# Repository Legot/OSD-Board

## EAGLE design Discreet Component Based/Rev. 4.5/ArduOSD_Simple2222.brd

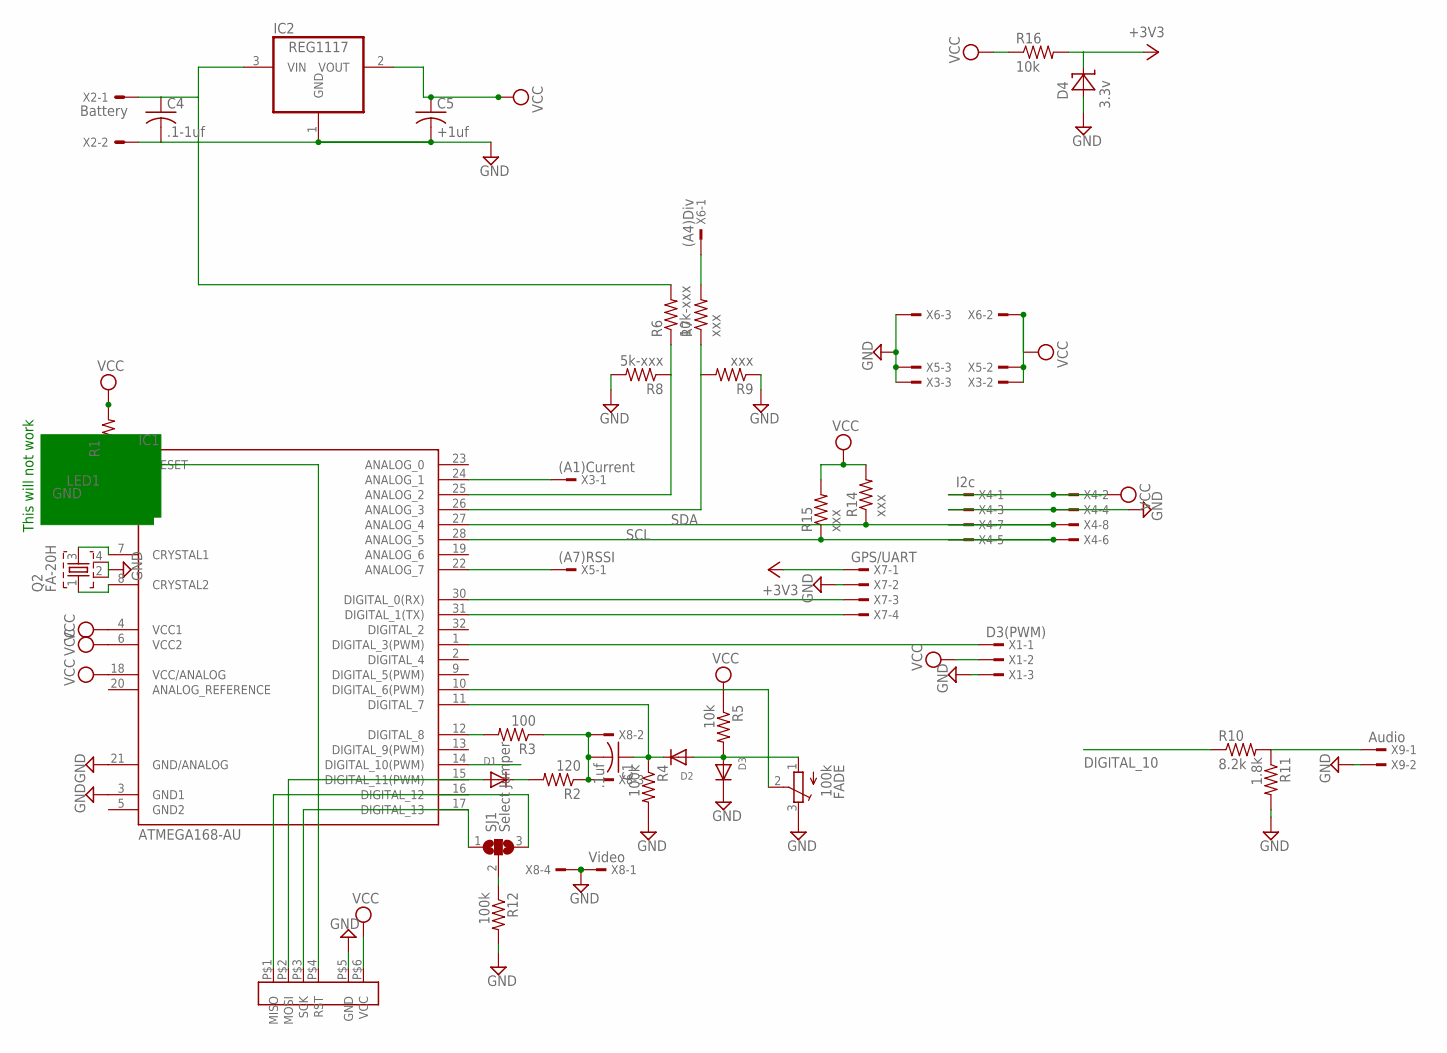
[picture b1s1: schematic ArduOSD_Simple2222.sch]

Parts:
C1: .1uf; C0805K
C4: .1-1uf; C0805K
C5: +1uf; C0805K
D1, D2, D3: DIODESOT23_WAVE; SOT23-W
D4: 3.3v; SOD-123
FADE: 100k; TC33X
IC1: ATMEGA168-AU; TQFP32-08
IC2: REG1117; SOT223
LED1: LEDCHIP-LED0805; CHIP-LED0805
Q2: FA-20H
R1: R-US_R0805; R0805
R2: 120; R0805
R3: 100; R0805
R4, R12: 100k; R0805
R5, R16: 10k; R0805
R6: 10k-xxx; R0805
R7, R9, R14, R15: xxx; R0805
R8: 5k-xxx; R0805
R10: 8.2k; R0805
R11: 1.8k; R0805
SJ1: Select Jumper; SJ_2
U$1: LIN_ISP; LINEAR_ISP
X1: D3(PWM); TSW-103-02-S-S
X2: Battery; 22-23-2021
X3: (A1)Current; TSW-103-02-S-S
X4: I2c; TSW-104-02-S-D-RA
X5: (A7)RSSI; TSW-103-02-S-S
X6: (A4)Div; TSW-103-02-S-S
X7: GPS/UART; TSW-104-02-S-S-RA
X8: Video; TSW-104-02-S-S-RA
X9: Audio; TSW-102-02-S-S-RA

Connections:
+3V3: D4.1 (C), R16.2, X7.1
AAAAAAAAAAAAHHHHHHHHHHHHH: R10.2, R11.1, X9.1
BATT_FPV: C4.1, IC2.3 (VIN), R6.2, X2.1
DIGITAL_10: IC1.14 (DIGITAL_10(PWM)), R10.1
GND: C4.2, C5.2, D3.3 (C), D4.2 (A), FADE.3 (E), IC1.3 (GND1), IC1.21 (GND/ANALOG), IC2.1 (GND), LED1.C, Q2.2, Q2.4, R4.2, R8.2, R9.1, R11.2, R12.2, U$1.P$5 (GND), X1.3, X2.2, X3.3, X4.3, X4.4, X5.3, X6.3, X7.2, X8.1, X8.4, X9.2
GND2: IC1.5 (GND2)
unnamed: IC1.29 (RESET), LED1.A, R1.1, U$1.P$4 (RST)
unnamed: D1.1 (A), IC1.15 (DIGITAL_11(PWM)), U$1.P$2 (MOSI)
unnamed: D1.3 (C), R2.2
unnamed: IC1.12 (DIGITAL_8), R3.2
unnamed: C1.2, R2.1, R3.1, X8.2, X8.3
unnamed: C1.1, D2.3 (C), IC1.11 (DIGITAL_7), R4.1
unnamed: D2.1 (A), D3.1 (A), FADE.1 (A), R5.2
unnamed: FADE.2 (S), IC1.10 (DIGITAL_6(PWM))
unnamed: IC1.26 (ANALOG_3), R7.1, R9.2
unnamed: IC1.7 (CRYSTAL1), Q2.3
unnamed: R12.1, SJ1.2
unnamed: R7.2, X6.1
unnamed: IC1.22 (ANALOG_7), X5.1
unnamed: IC1.16 (DIGITAL_12), SJ1.3, U$1.P$1 (MISO)
unnamed: IC1.17 (DIGITAL_13), SJ1.1, U$1.P$3 (SCK)
unnamed: IC1.24 (ANALOG_1), X3.1
unnamed: IC1.1 (DIGITAL_3(PWM)), X1.1
unnamed: IC1.25 (ANALOG_2), R6.1, R8.1
unnamed: IC1.8 (CRYSTAL2), Q2.1
RX: IC1.30 (DIGITAL_0(RX)), X7.3
SCL: IC1.28 (ANALOG_5), R15.1, X4.5, X4.6
SDA: IC1.27 (ANALOG_4), R14.1, X4.7, X4.8
TX: IC1.31 (DIGITAL_1(TX)), X7.4
VCC: C5.1, IC1.4 (VCC1), IC1.6 (VCC2), IC1.18 (VCC/ANALOG), IC2.2 (VOUT), R1.2, R5.1, R14.2, R15.2, R16.1, U$1.P$6 (VCC), X1.2, X3.2, X4.1, X4.2, X5.2, X6.2

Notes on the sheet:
This will not work

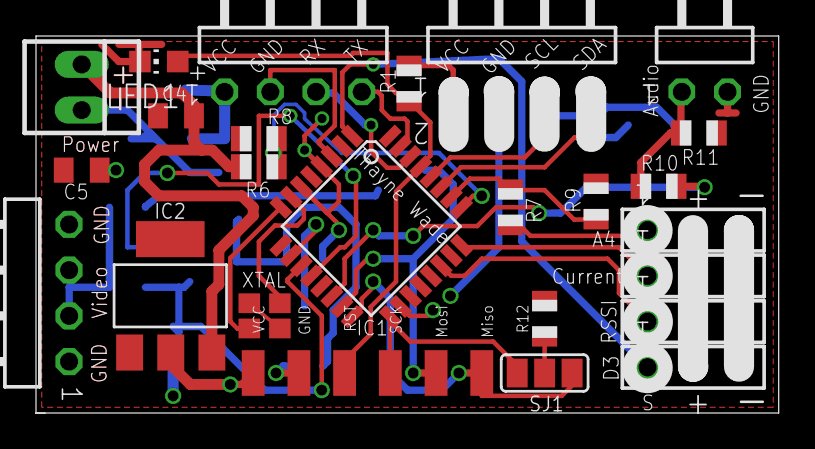
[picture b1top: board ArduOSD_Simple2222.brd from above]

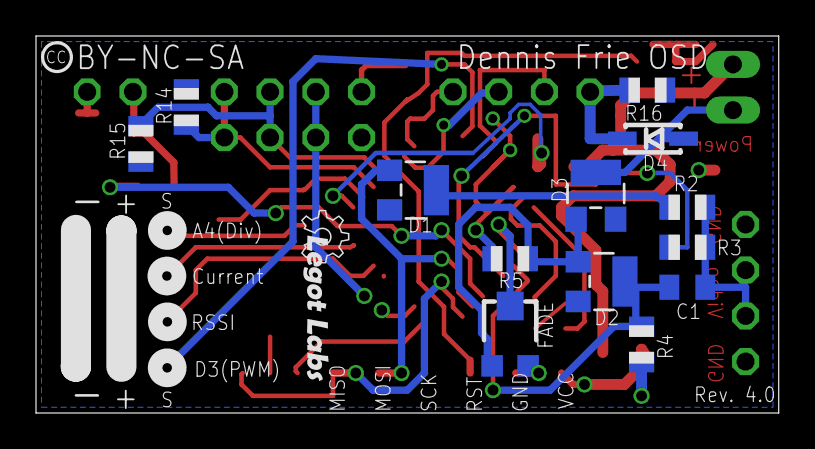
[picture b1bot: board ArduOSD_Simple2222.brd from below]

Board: 2 copper layers, 41.3 x 20.9 mm, 38 parts (13 on the bottom side), 29 nets.

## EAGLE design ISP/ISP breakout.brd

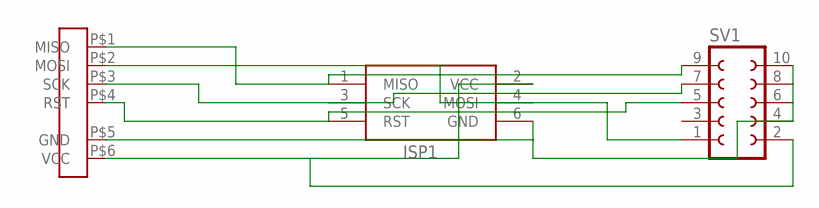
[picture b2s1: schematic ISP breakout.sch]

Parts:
ISP1: AVRISP-6; AVRISP
SV1: FE05-2
U$1: LIN_ISP; LINEAR_ISP

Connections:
unnamed: ISP1.2 (VCC), SV1.2, U$1.P$6 (VCC)
unnamed: ISP1.4 (MOSI), SV1.1, U$1.P$2 (MOSI)
unnamed: ISP1.1 (MISO), SV1.9, U$1.P$1 (MISO)
unnamed: ISP1.3 (SCK), SV1.7, U$1.P$3 (SCK)
unnamed: ISP1.5 (RST), SV1.5, U$1.P$4 (RST)
unnamed: ISP1.6 (GND), SV1.4, SV1.6, SV1.8, SV1.10, U$1.P$5 (GND)

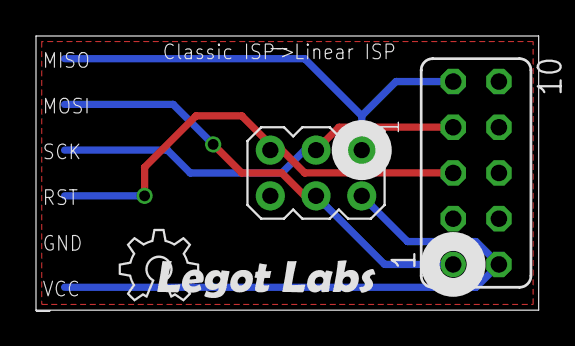
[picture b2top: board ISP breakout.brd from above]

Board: 2 copper layers, 27.9 x 15.2 mm, 3 parts (1 on the bottom side), 6 nets.

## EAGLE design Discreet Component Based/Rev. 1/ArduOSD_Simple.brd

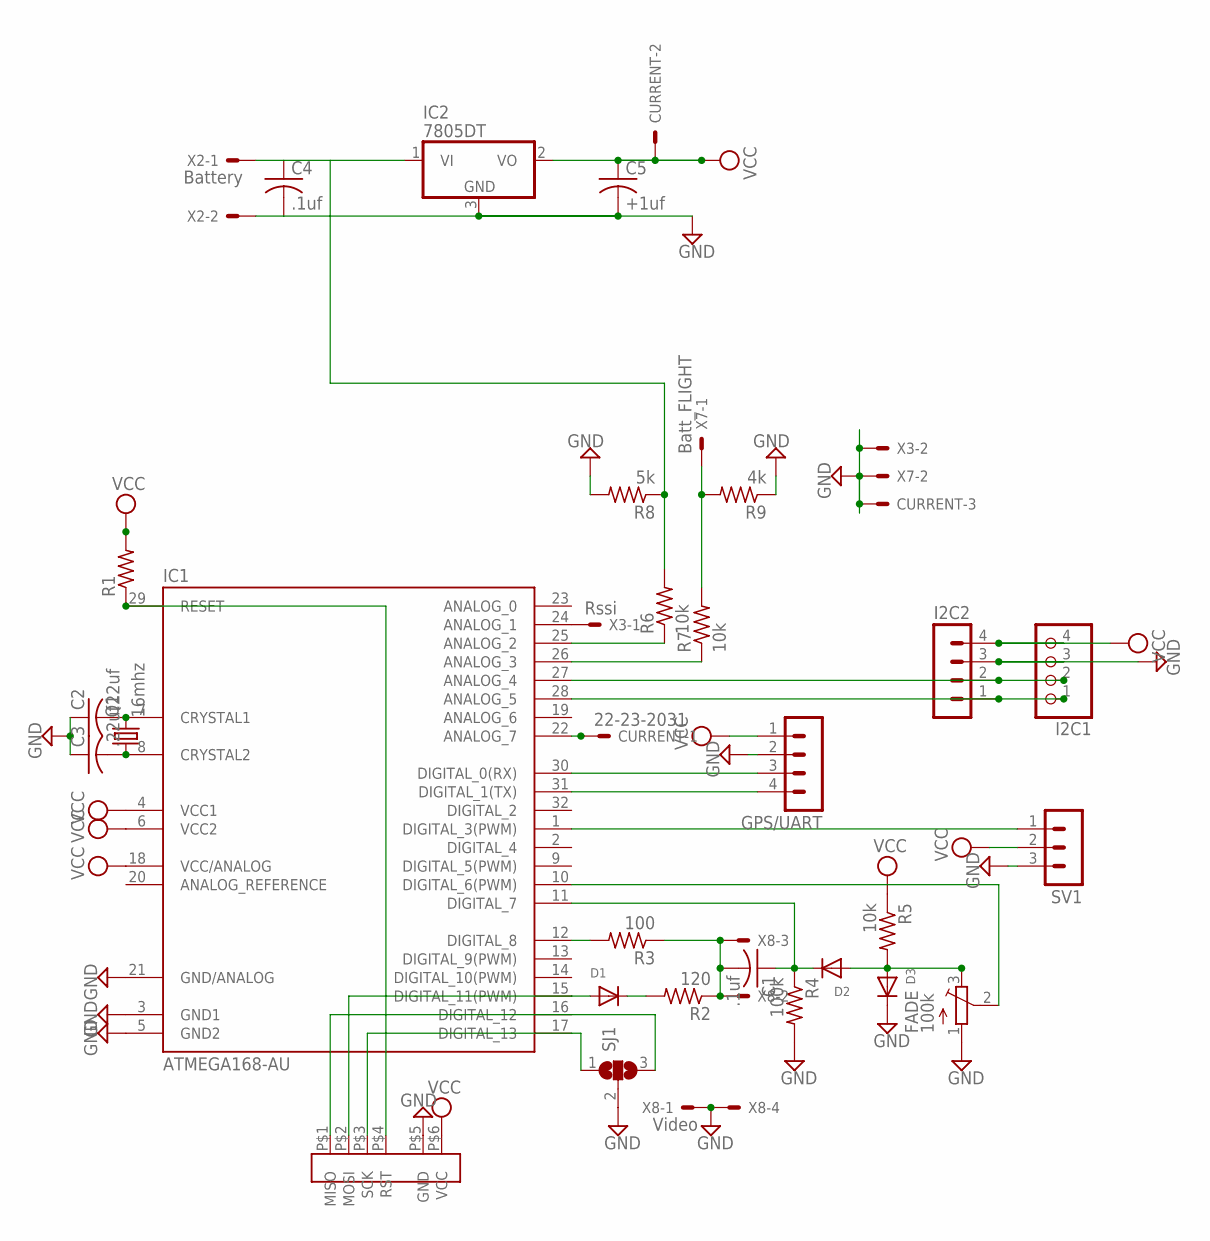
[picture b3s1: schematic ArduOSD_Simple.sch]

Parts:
C1, C4: .1uf; C0805K
C2, C3: .22uf; C0805K
C5: +1uf; C0805K
CURRENT: 22-23-2031
D1, D2, D3: DIODESOT23_WAVE; SOT23-W
FADE: 100k; TC33X
GPS/UART: MA04-1
I2C1: PINHD-1X4; 1X04
I2C2: MA04-1
IC1: ATMEGA168-AU; TQFP32-08
IC2: 7805DT; TO252
Q1: 16mhz; CSM-7X-DU
R1: R-US_R0805; R0805
R2: 120; R0805
R3: 100; R0805
R4: 100k; R0805
R5, R6, R7: 10k; R0805
R8: 5k; R0805
R9: 4k; R0805
SJ1: SJ2W; SJ_2
SV1: MA03-1
U$1: LIN_ISP; LINEAR_ISP
X2: Battery; 22-23-2021
X3: Rssi; 22-23-2021
X7: Batt_FLIGHT; 22-23-2021
X8: Video; 22-23-2041

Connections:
BATT_FPV: C4.1, IC2.1 (VI), R6.2, R8.1, X2.1
GND: C2.1, C3.1, C4.2, C5.2, CURRENT.3, D3.3 (C), FADE.1 (A), GPS/UART.2, I2C1.3, I2C2.3, IC1.3 (GND1), IC1.5 (GND2), IC1.21 (GND/ANALOG), IC2.3 (GND), R4.2, R8.2, R9.1, SJ1.2, SV1.3, U$1.P$5 (GND), X2.2, X3.2, X7.2, X8.1, X8.4
GPS_DAT: GPS/UART.3, IC1.30 (DIGITAL_0(RX))
unnamed: IC1.29 (RESET), R1.1, U$1.P$4 (RST)
unnamed: D1.1 (A), IC1.15 (DIGITAL_11(PWM)), U$1.P$2 (MOSI)
unnamed: D1.3 (C), R2.2
unnamed: IC1.12 (DIGITAL_8), R3.2
unnamed: C1.2, R2.1, R3.1, X8.2, X8.3
unnamed: C1.1, D2.3 (C), IC1.11 (DIGITAL_7), R4.1
unnamed: D2.1 (A), D3.1 (A), FADE.3 (E), R5.2
unnamed: FADE.2 (S), IC1.10 (DIGITAL_6(PWM))
unnamed: GPS/UART.4, IC1.31 (DIGITAL_1(TX))
unnamed: IC1.26 (ANALOG_3), R7.1
unnamed: C2.2, IC1.7 (CRYSTAL1), Q1.2
unnamed: C3.2, IC1.8 (CRYSTAL2), Q1.1
unnamed: IC1.25 (ANALOG_2), R6.1
unnamed: IC1.24 (ANALOG_1), X3.1
unnamed: IC1.16 (DIGITAL_12), SJ1.3, U$1.P$1 (MISO)
unnamed: IC1.17 (DIGITAL_13), SJ1.1, U$1.P$3 (SCK)
unnamed: CURRENT.1, IC1.22 (ANALOG_7)
unnamed: IC1.1 (DIGITAL_3(PWM)), SV1.1
unnamed: R7.2, R9.2, X7.1
SCL: I2C1.1, I2C2.1, IC1.28 (ANALOG_5)
SDA: I2C1.2, I2C2.2, IC1.27 (ANALOG_4)
VCC: C5.1, CURRENT.2, GPS/UART.1, I2C1.4, I2C2.4, IC1.4 (VCC1), IC1.6 (VCC2), IC1.18 (VCC/ANALOG), IC2.2 (VO), R1.2, R5.1, SV1.2, U$1.P$6 (VCC)

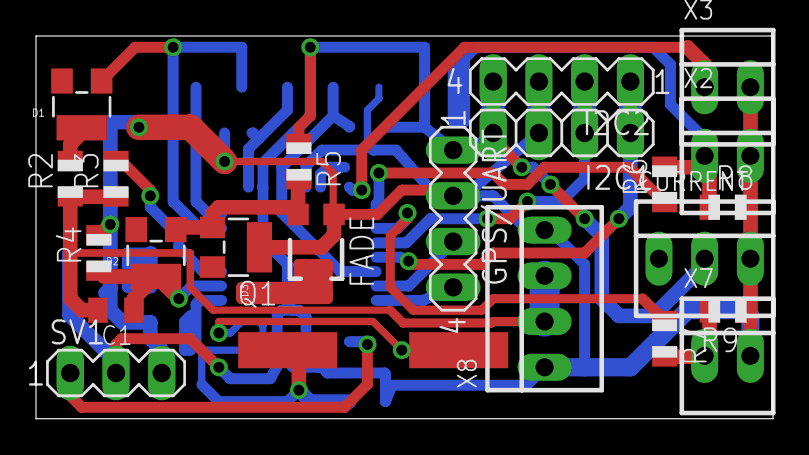
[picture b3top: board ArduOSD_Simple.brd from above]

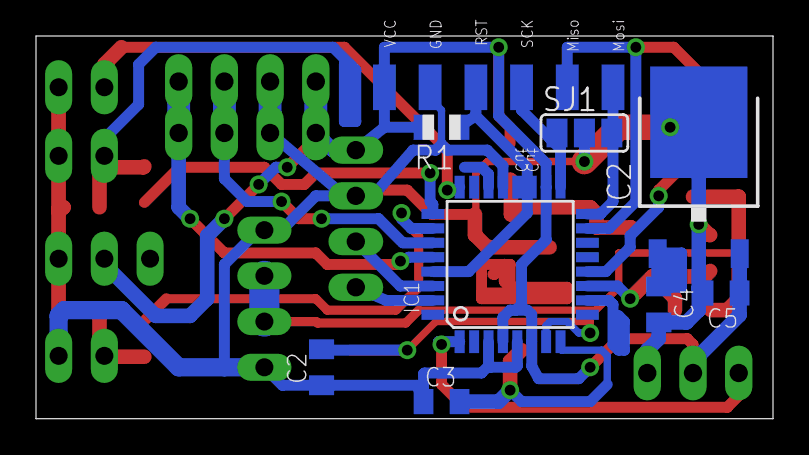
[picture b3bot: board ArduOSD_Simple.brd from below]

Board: 2 copper layers, 40.9 x 21.3 mm, 32 parts (9 on the bottom side), 25 nets.

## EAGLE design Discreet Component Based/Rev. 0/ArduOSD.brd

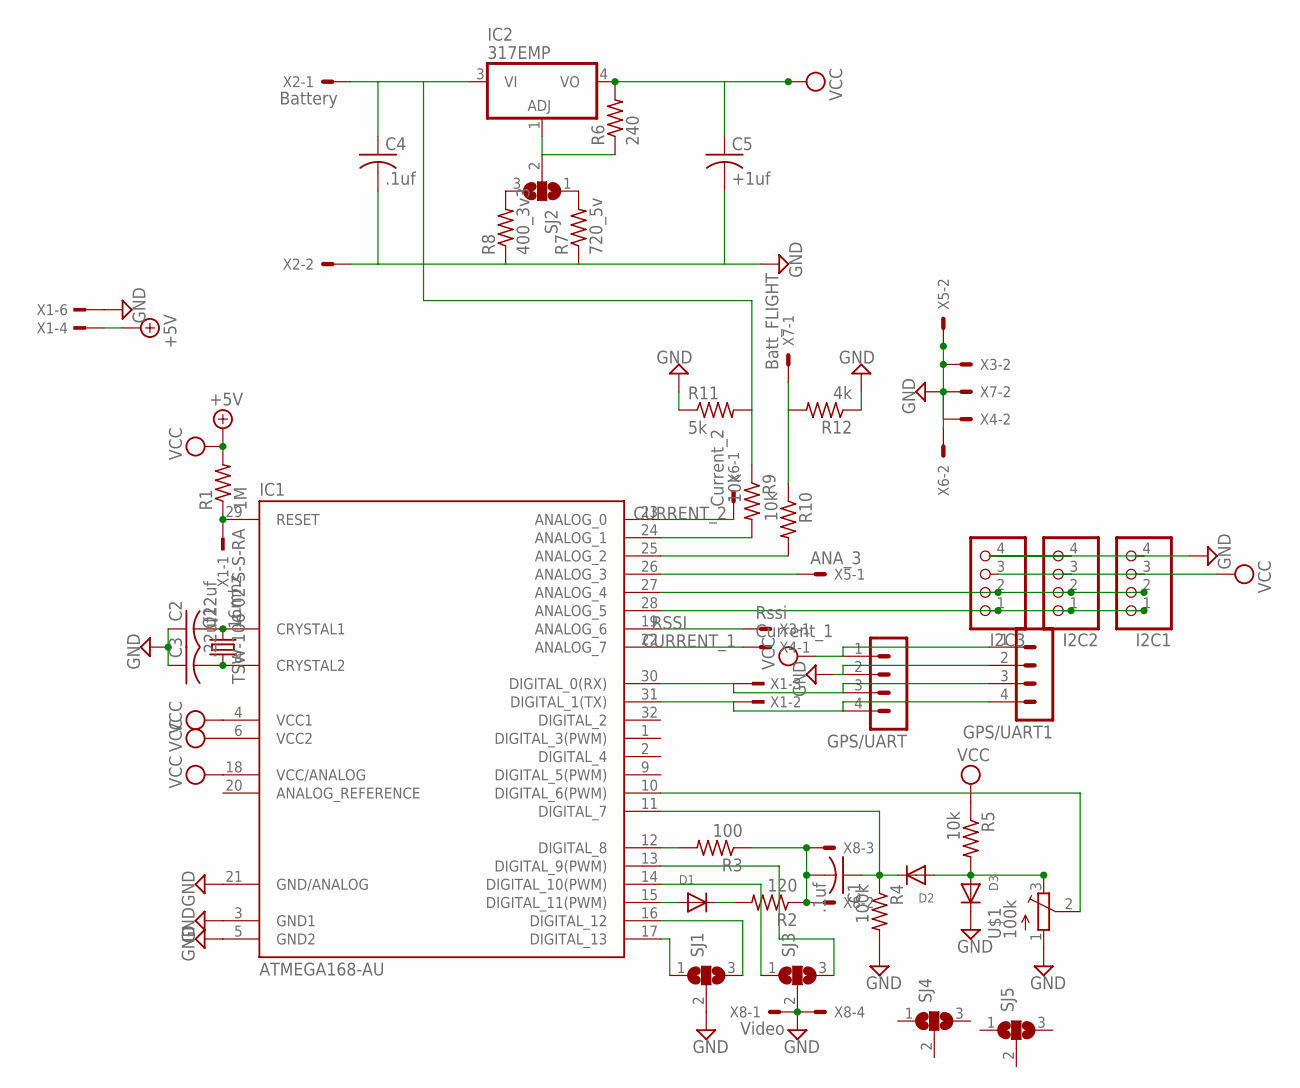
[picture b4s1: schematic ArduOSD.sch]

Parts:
C1, C4: .1uf; C0805K
C2, C3: .22uf; C0805K
C5: +1uf; C025-060X050
D1, D2, D3: DIODESOT23_WAVE; SOT23-W
GPS/UART, GPS/UART1: MA04-1
I2C1, I2C2, I2C3: PINHD-1X4; 1X04
IC1: ATMEGA168-AU; TQFP32-08
IC2: 317EMP; SOT223
Q1: 16mhz; CSM-7X-DU
R1: 1M; M0805
R2: 120; M0805
R3: 100; M0805
R4: 100k; M0805
R5, R9, R10: 10k; M0805
R6: 240; R0805
R7: 720_5v; R0805
R8: 400_3v3; R0805
R11: 5k; M0805
R12: 4k; M0805
SJ1, SJ2, SJ3, SJ4, SJ5: SJ2W; SJ_2
U$1: 100k; TC33X
X1: TSW-106-02-S-S-RA
X2: Battery; 22-23-2021
X3: Rssi; 22-23-2021
X4: Current_1; 22-23-2021
X5: ANA_3; 22-23-2021
X6: Current_2; 22-23-2021
X7: Batt_FLIGHT; 22-23-2021
X8: Video; 22-23-2041

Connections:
+5V: X1.4
ANA_3: IC1.26 (ANALOG_3), X5.1
BATT_FPV: C4.1, IC2.3 (VI), R9.1, R11.2, X2.1
CURRENT_1: IC1.22 (ANALOG_7), X4.1
CURRENT_2: IC1.23 (ANALOG_0), X6.1
GND: C2.1, C3.1, C4.2, C5.2, D3.3 (C), GPS/UART.2, GPS/UART1.2, I2C1.4, I2C2.4, I2C3.4, IC1.3 (GND1), IC1.5 (GND2), IC1.21 (GND/ANALOG), R4.2, R7.1, R8.1, R11.1, R12.1, SJ1.2, SJ3.2, U$1.1 (A), X1.6, X2.2, X3.2, X4.2, X5.2, X6.2, X7.2, X8.1, X8.4
GPS_DAT: GPS/UART.3, GPS/UART1.3, IC1.30 (DIGITAL_0(RX)), X1.3
unnamed: IC1.29 (RESET), R1.1, X1.1
unnamed: D1.1 (A), IC1.15 (DIGITAL_11(PWM))
unnamed: D1.3 (C), R2.2
unnamed: IC1.12 (DIGITAL_8), R3.2
unnamed: C1.2, R2.1, R3.1, X8.2, X8.3
unnamed: C1.1, D2.3 (C), IC1.11 (DIGITAL_7), R4.1
unnamed: D2.1 (A), D3.1 (A), R5.2, U$1.3 (E)
unnamed: IC1.10 (DIGITAL_6(PWM)), U$1.2 (S)
unnamed: GPS/UART.4, GPS/UART1.4, IC1.31 (DIGITAL_1(TX)), X1.2
unnamed: C2.2, IC1.7 (CRYSTAL1), Q1.2
unnamed: C3.2, IC1.8 (CRYSTAL2), Q1.1
unnamed: IC1.25 (ANALOG_2), R10.2
unnamed: IC1.24 (ANALOG_1), R9.2
unnamed: IC1.16 (DIGITAL_12), SJ1.3
unnamed: IC1.17 (DIGITAL_13), SJ1.1
unnamed: IC2.1 (ADJ), R6.1, SJ2.2
unnamed: R7.2, SJ2.1
unnamed: R10.1, R12.2, X7.1
unnamed: R8.2, SJ2.3
unnamed: IC1.14 (DIGITAL_10(PWM)), SJ3.1
unnamed: IC1.13 (DIGITAL_9(PWM)), SJ3.3
RSSI: IC1.19 (ANALOG_6), X3.1
SCL: I2C1.1, I2C2.1, I2C3.1, IC1.28 (ANALOG_5)
SDA: I2C1.2, I2C2.2, I2C3.2, IC1.27 (ANALOG_4)
VCC: C5.1, GPS/UART.1, GPS/UART1.1, I2C1.3, I2C2.3, I2C3.3, IC1.4 (VCC1), IC1.6 (VCC2), IC1.18 (VCC/ANALOG), IC2.4 (VO), R1.2, R5.1, R6.2

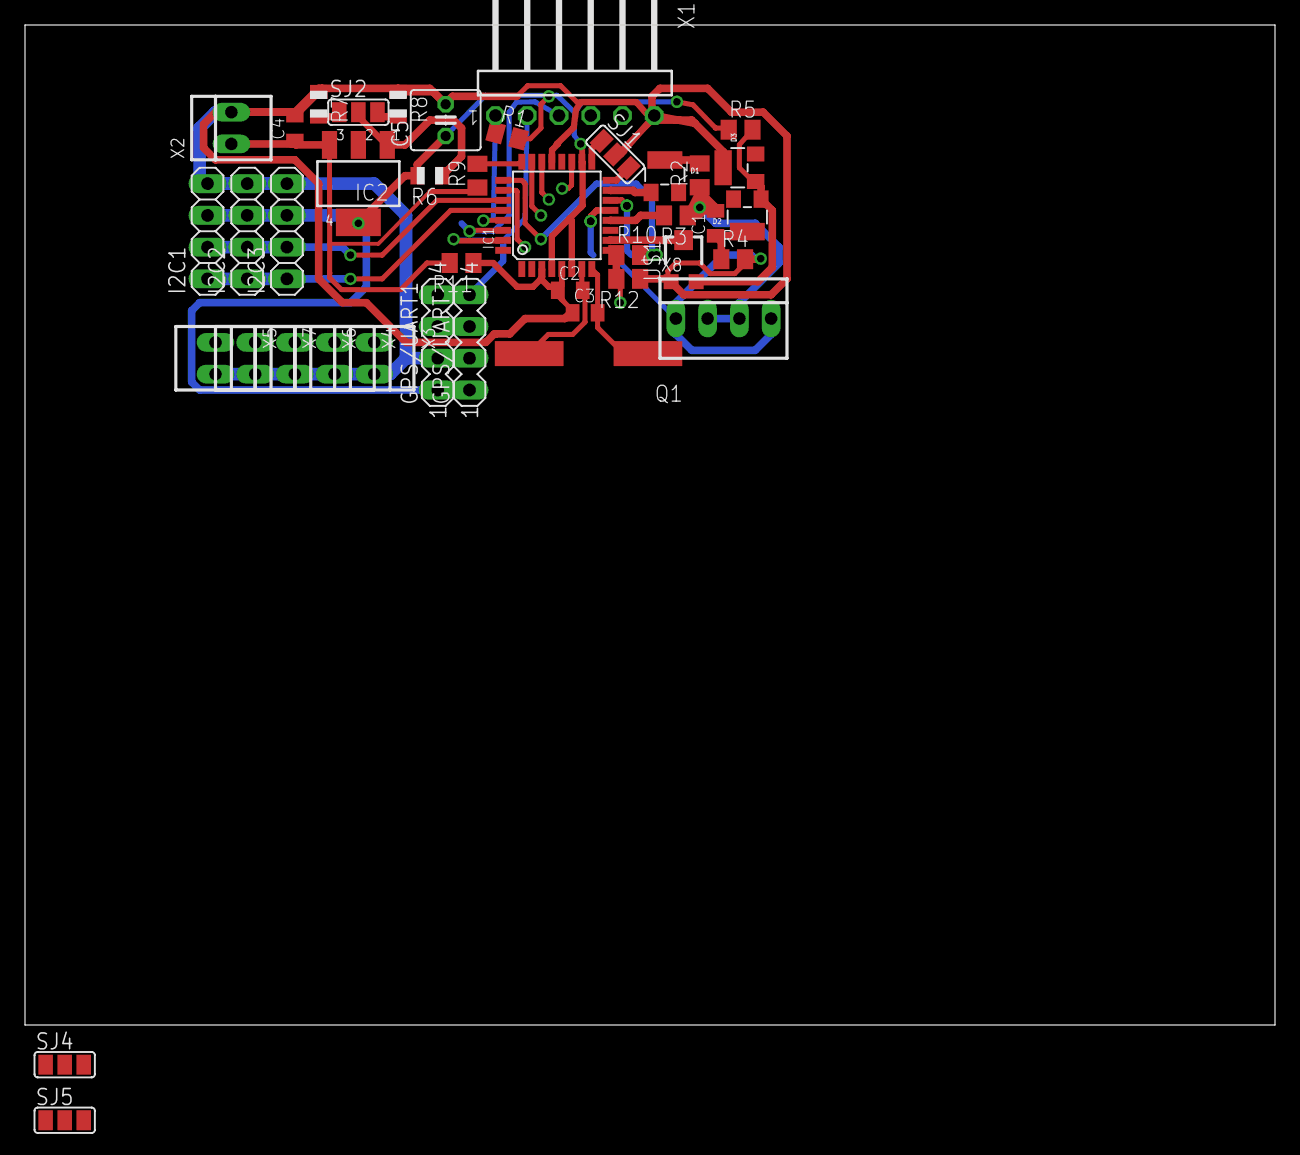
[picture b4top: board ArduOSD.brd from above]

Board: 2 copper layers, 100.0 x 80.0 mm, 42 parts (1 on the bottom side), 31 nets.

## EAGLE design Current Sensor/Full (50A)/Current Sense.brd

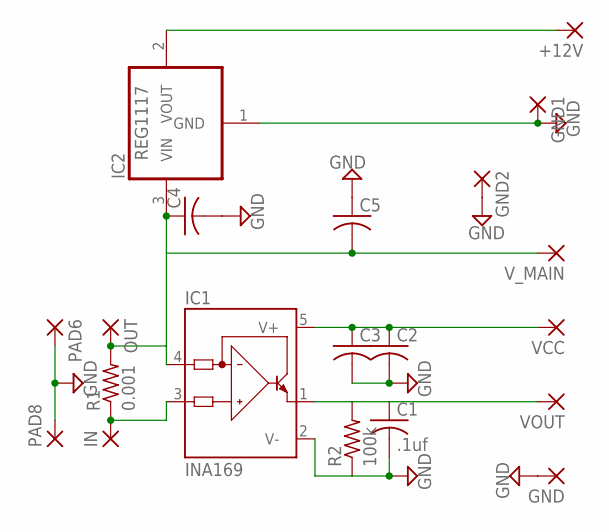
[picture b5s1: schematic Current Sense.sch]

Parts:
+12V: SMD2; SMD1,27-2,54
C1: .1uf; C0805K
C2, C3, C4, C5: C-USC0805K; C0805K
GND, GND1, GND2: SMD2; SMD1,27-2,54
IC1: INA169; SOT23-5
IC2: REG1117; SOT223
IN: SMD5; SMD2,54-5,08
OUT: SMD5; SMD2,54-5,08
PAD6, PAD8: SMD5; SMD2,54-5,08
R1: 0.001; R2512
R2: 100k; R0805
VCC: SMD2; SMD1,27-2,54
VOUT: SMD2; SMD1,27-2,54
V_MAIN: SMD2; SMD1,27-2,54

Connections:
+12V: +12V.1, IC2.2 (VOUT)
GND: C1.2, C2.2, C3.2, C4.2, C5.1, GND.1, GND1.1, GND2.1, IC1.2 (V-), IC2.1 (GND), PAD6.1, PAD8.1, R2.1
unnamed: IC1.3 (IN+), IN.1, R1.1
unnamed: C1.1, IC1.1 (OUT), R2.2, VOUT.1
OUT: C4.1, C5.2, IC1.4 (IN-), IC2.3 (VIN), OUT.1, R1.2, V_MAIN.1
VCC: C2.1, C3.1, IC1.5 (V+), VCC.1

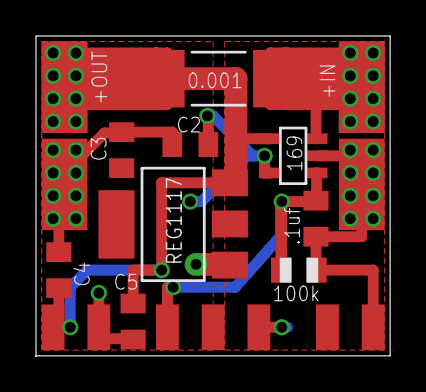
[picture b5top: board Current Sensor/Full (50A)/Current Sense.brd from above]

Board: 2 copper layers, 19.7 x 17.8 mm, 20 parts (0 on the bottom side), 6 nets.

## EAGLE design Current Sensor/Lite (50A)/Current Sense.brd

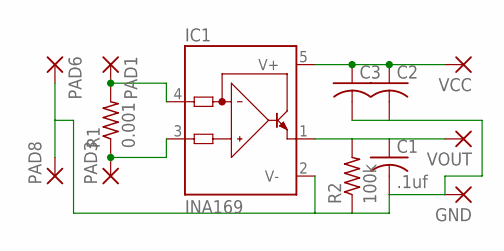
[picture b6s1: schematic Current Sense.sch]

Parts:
C1: .1uf; C0805K
C2, C3: C-USC0805K; C0805K
GND: SMD2; SMD1,27-2,54
IC1: INA169; SOT23-5
PAD1, PAD3, PAD6, PAD8: SMD5; SMD2,54-5,08
R1: 0.001; R2512
R2: 100k; R0805
VCC: SMD2; SMD1,27-2,54
VOUT: SMD2; SMD1,27-2,54

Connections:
unnamed: IC1.3 (IN+), PAD3.1, R1.1
unnamed: C1.2, C2.2, C3.2, GND.1, IC1.2 (V-), PAD6.1, PAD8.1, R2.1
unnamed: C1.1, IC1.1 (OUT), R2.2, VOUT.1
unnamed: C2.1, C3.1, IC1.5 (V+), VCC.1
OUT: IC1.4 (IN-), PAD1.1, R1.2; also elsewhere on the board

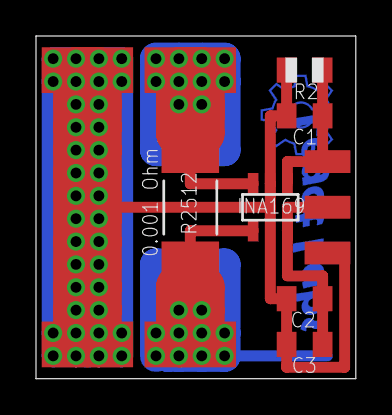
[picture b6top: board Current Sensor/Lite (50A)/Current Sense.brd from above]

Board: 2 copper layers, 17.8 x 19.0 mm, 14 parts (1 on the bottom side), 5 nets.

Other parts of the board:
VOLTAGE: SMD1,27-2,54

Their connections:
OUT: VOLTAGE.1; also elsewhere on the board

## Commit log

2012-10-05 These are under Creative Commons BY-NC-SA
    A PCB based on Dennis Frie's arduino based open source OSD.
2012-10-07 BY-NC-SA
2012-10-08 Added Renders
2012-10-09 Changed Current Sensors
2012-10-22 Updated to V4.0
2012-10-22 Names
2012-10-22 Cleaning
2012-11-13 Ultra Cleanup & Update

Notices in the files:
Current Sensor/Full (50A)/Current Sense.brd:
CC-BY-NC-SA
